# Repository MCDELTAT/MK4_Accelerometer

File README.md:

## Prusa MK4 Accelerometer

If you're reading this it's likely because you've [noticed][3] that your MK4 xBuddy Controller has a port reserved for an accelerometer and wondered "Hmmm. I wonder if that works."

I'm happy to report that the answer is "Yes." I found it to be reliable and working just fine, but in response to my demo, Josef Prusa himself responded "Hi! Please note the code is not tested on MK4 so you shouldn't count on it's results. There will be an official implementation but not ETA yet." Source [here][4].

This repository contains information, designs, and tools for using an accelerometer with the Prusa MK4 3D Printer.

This primary document is focused on being a quick start guide, while other documents in the repository contain more in-depth technical information about other aspects of the project.

## Future Work
Here's a roadmap of a few simple tasks that I'd like to accomplish with this project.

- [x] Design mounts for the Toolhead and Bed that work with both custom and off the shelf boards.
- [x] Test other chips like the LIS3DH for compatibility.
- [ ] Run print tests and document outcomes (IN PROGRESS)
- [ ] Design our own custom PCB with a compatible Molex Clik-MATE connector (IN PROGRESS-Design Complete, Validation Underway)
    * This will allow users to install an accelerometer quickly and without all the tools needed to solder.

## Compatability
* At the moment, only MCDELTAT has confirmed the accelerometer as working on firmware versions 5.2.1 and 6.0.0. Their printer uses the 2021 0.2.7 xBuddy board. Two other community members have tried on printers that use the 0.3.7 board and are not seeing similar signals on their ports. I'm working with them and hoping Prusa will release the older schematics so I can compare.

## ⚠️ HALT - Warranty Check
Q: Does this void my warranty?

A: Probably.

You can read the official Prusa Warranty on their website [here][1]. Quote "This warranty is **voided by:** ... Upgrades or add-ons that are not officially supported."

This modification does not require you to compile or upload any custom firmware to work. The release firmware directly from Prusa supports these boards, so this is purely a hardware addition. That said, I will include thorough warnings where appropriate to ensure that nothing goes wrong, should you follow the instructions correctly.

## Tools and Part Requirements
Here is a list of tools that will be needed to add an accelerometer board at the moment.
1. Clik-MATE 6 Pin Cable Assembly (MPN: 0151350606 for 600mm). Digikey [source][2]
2. LIS2DH Accelerometer board ready for SPI communication.
    * See the table below for a table of boards that have been tested and verified as working.
3. Soldering Iron and related tools.
4. (Optional) A multimeter will be helpful.
5. Mounts for the board. 3D Printable mounts for the X and Y-Axis can be found [here][9]. The mounts are designed for MK4 printers, but the mounting tray is designed to be modular. At the moment the only tray is for the generic accelerometer boards. I will provide another tray for my custom board later.
6. Some kind of computer capable of controlling your MK4 Printer and a USB-C Cable. I tested everything with a Raspberry Pi running Octoprint, but any compatible software should be functional. For example, Mainsail or Pronterface should be more than capable.

## Soldering Your Accelerometer Board
For this section, I will document the soldering procedure for the generic purple Chinese LIS2DH boards, as that is the first board I confirmed to be working.

1. Power off your printer. Unplug it from it's power source. 
2. (Optional but recommended). Insert one end of your cable assembly into the Accelerometer port of the board. The connector is keyed and will only fit one direction, with the release arm facing towards the center of the board (back of the printer). Pull it back out and use a marker to color the top side of the connector. This will help you to keep track of which pin belongs to each cable.
3. Cut the cable assembly with a wire stripper or other tool. Goodbye beautiful connector.
4. Strip off approximately 5mm of the outer wire insulator for each cable.
5. (Optional tinning technique). Heat up your soldering iron, twist the stranded wires of a single cable together tightly, and apply solder to the wires. This makes it into one solid connector and makes it easier to solder to the accelerometer board later.
6. Identify the first wire to solder. If you did step two, the top side that you marked is pin 6 on the Prusa Schematics and Connector documentation. (See the Diagram below). On the Digikey cable assembly, they use tape in the middle of the cables to group them to together. We have two options:

    a) Cut the tape and visually trace the cables.

    b) Leave the tape intact and use a multimeter to buzz out which cable is connected to each connector pin. This can be done by switching to continuity mode, touching one lead to a cable of your choice, and the other to small pad on the back of the connector.
7. Solder the wire to the correct position. Repeat steps 5 and 6, finding the correct wires and soldering them to the board. A table is provided below for reference.
8. Snip the extra wire that wasn't covered by the solder joint.

## Pinout
Here is a reference table for the Prusa Connector Pins and the breakout board. Prusa's documentation supporting this is found [here][5].

| Connector           | Pin (Prusa) | Pin (Accel Board) | Type              | Function | GPIO | Limitations  |
|---------------------|-------------|-------------------|-------------------|----------|------|--------------|
| J29 (ACCELEROMETER) | 1           | CS                | open drain output | SPI2 CS  | PA10 | Max 3.3V/5mA |
| J29 (ACCELEROMETER) | 2           | SCL               | input/output      | SPI2 SCL | PB10 | Max 5V/5mA   |
| J29 (ACCELEROMETER) | 3           | SDA               | input/output      | SPI2 SDI | PC3  | Max 5V/5mA   |
| J29 (ACCELEROMETER) | 4           | SDO               | input/output      | SPI2 SDO | PC2  | Max 5V/5mA   |
| J29 (ACCELEROMETER) | 5           | VCC               | 3V3               | Power    | x    | Max 50mA     |
| J29 (ACCELEROMETER) | 6           | GND               | GND               | Power    | x    | x            |

## Pinout Images
### Connector Side:

### Adafruit Board:

### Generic LIS2DH Board:

## Compatible Boards:

| Board Name                                | Testing Status | Source                                          | Notes                                                                                                                                                                                                                                                                                                       |
|-------------------------------------------|----------------|-------------------------------------------------|-------------------------------------------------------------------------------------------------------------------------------------------------------------------------------------------------------------------------------------------------------------------------------------------------------------|
| NOYITO LIS2DH12TR Development Board       | WORKING        | https://a.co/d/4UiPgB6                          | This board is very generic and can be found many places ranging from $4 to $13. They likely all come from the same place.                                                                                                                                                                                   |
| Sparkfun SPX-15760 LIS2DH12 (Qwiic)       | FAIL           | https://www.sparkfun.com/products/retired/15760 | This board is hard wired for I2C, while the Prusa MK4 expects an SPI compatible device, so this will not work.                                                                                                                                                                                              |
| Adafruit LIS3DH Triple-Axis Accelerometer (Recommended) | WORKING   | https://www.adafruit.com/product/2809           | The LIS3DH has a few more features we won't be using, however I confirmed it to work similarly. Since Adafruit has a solid supply chain, this is likely the best all around choice. Minor Con: The breakout board has pins on both sides, requiring cables to be on both sides, so it is a little messier.

## Using the Accelerometer
If you are hoping to get useful values out of the accelerometer, emphasize doing any pending maintenance first. Lube the smooth rods/bearings. Check for scratches. Check belt tension, etc. Each of these factors will change these results if you fix them later, so just do them now to avoid retesting. See Prusa's official docs for recommended regular maintenance [here][8].

1. Once you are confident your connections are going to the correct pins, plug the accelerometer into the MK4 Buddy board and the mounts.
2. Connect to the printer over USB-C to issue GCODE.
3. ⚠️ **IMPORTANT STEP** Before setting any parameters, gather the values that Prusa originally set on the printer. This will allow you to roll back to those values later if you want. In a GCODE control window, issue the `M593` command with no arguments. This will return the existing Input Shaping (IS) parameters. An example of my output can be found below. If you want to see all my Input Shaping testing results, see [Testing][6].
```
Send: M593
Recv: echo:axis X type=MZV freq=50.700001 damp=0.100000 vr=20.000000
Recv: echo:axis Y type=MZV freq=40.599998 damp=0.100000 vr=20.000000
Recv: echo:axis Z disabled
Recv: echo:weight_adjust y freq_delta=-20.000000 mass_limit=800.000000
Recv: ok
```
4. Issue the following command `M959 X F40.0 G60.0 N10`. This tests the X-Axis starting at 40Hz and ending at 60Hz, with a very quick sample size. The results this produces should not be used. It is provided here purely as a way to quickly test that you wired up the sensor correctly.
5. Now to test the X-Axis, you likely want to run the default workflow, which is over a large frequency range and sample size.
6. The command above gave us a general range, but now we can confirm a second time by running it over a smaller range with more samples. For example, if step 5 returned a frequency of 79.0Hz, then I can test from 65 to 85Hz, at steps of 0.5Hz, with 100 Samples. This can be done with the command `M959 X F65.0 G85.0 H0.5`. See below for a list of parameters to the M959 command.
7. Once you are satisfied with the results and think you have a consistent number, we will save the values. See the official documentation for the `M593` command [here][7]. Assuming I got the following results `Recv: ZV shaper selected Recv: Frequency: 79.00 damping ratio: 0.17444`

    a) To do this temporarily (until you shut off the printer), run the following command `M593 X D0.17444 F79.00 T0`. Note the lack of the `W` parameter, the parameter to save it to the EEPROM.

    b) To save it permanently, run the following command `M593 X D0.17444 F79.00 T0 W`.

## M959 Command
The `M959` command does all the heavy lifting in our testing. It's parameters are only listed in the source code, so I've copied them here for convenience.
```
/\*\*  
 \* u/brief Tune input shaper  
 \*  
 \* - X<direction> Vibrate with X motor, start in direction 1 or -1  
 \* - Y<direction> Vibrate with Y motor, start in direction 1 or -1  
 \* - Z<direction> Vibrate with Z motor, start in direction 1 or -1  
 \* - K           select Klipper tune algorithm  
 \* - KM          select Klipper Marek modified tune algorithm  
 \* - F<Hz>       Start frequency  
 \* - G<Hz>       End frequency  
 \* - H<Hz>       Frequency step  
 \* - A<mm/s-2>   Acceleration  
 \* - N<cycles>   Number of excitation signal periods  
 \*               of active measurement.  
 \*/  
```

[1]: https://help.prusa3d.com/article/warranty_2288
[2]: https://www.digikey.com/en/products/detail/molex/0151350606/6830172
[3]: https://help.prusa3d.com/article/accessory-connectors-mk4_622345
[4]: https://www.reddit.com/r/prusa3d/comments/1b5wych/comment/ktben9d/?utm_source=share&utm_medium=web2x&context=3
[5]: https://help.prusa3d.com/article/accessory-connectors-mk4_622345
[6]: ./Testing.md
[7]: https://help.prusa3d.com/article/buddy-firmware-specific-g-code-commands_633112#m-codes
[8]: https://help.prusa3d.com/article/regular-printer-maintenance-mk4_419000
[9]: https://www.printables.com/model/839201-mk4-accelerometer-mounts-for-x-and-y-axis-input-sh

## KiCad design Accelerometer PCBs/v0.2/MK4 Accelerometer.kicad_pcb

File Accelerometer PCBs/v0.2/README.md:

## Prusa MK4 Accelerometer v0.2

🛑 Status: Design complete, have ordered PCBs, have not tried on a real printer.

This board design fixes a large error made in the last revision, namely, the pinout is correct for a stock cable purchased from Digikey. Thus you should be able to buy cables from them, and immediately plug it into your printer. I also moved a silkscreen around the LIS2DH chip for hopefully better visual alignment. Finally, as reported in issue #1 of the repo, a 2.2K may be added to make this circuit compatible with 0.3.7 and 0.4.4 boards.

This is the bare minimum reference circuit as provided by STMicroelectronics, with an LED for reference.

BOM:
| Label | Digikey Part Num       | Quantity | Description                        |
| ----- | ---------------------- | -------- | ---------------------------------- |
| C1    | 1292-0201X104K250CT-ND | 1        | 0603 100nF Ceramic Capacitor       |
| C2    | CL10A106MQ8NNNC        | 1        | 0603 10uF Ceramic Capacitor        |
| D1    | IN-S63AT5G             | 1        | 0603 Green LED 525nm               |
| R1    | RC0603FR-07120RL       | 1        | 0603 120Ohm Resistor 1/10W         |
| R2    | ERJ-H3GJ222V           | 1        | 0603 2.2K Resistor Panasonic 1/8W  |
| J1    | 5025840670             | 1        | Molex Clickmate 6Pin SMT Connector |
| U1    | LIS2DHTR               | 1        | LIS2DHTR MEMS Accelerometer        |

When aligning the LIS2DHTR by hand, make sure the circle is in the top right corner, matching the stars near the LGA-12 pads.

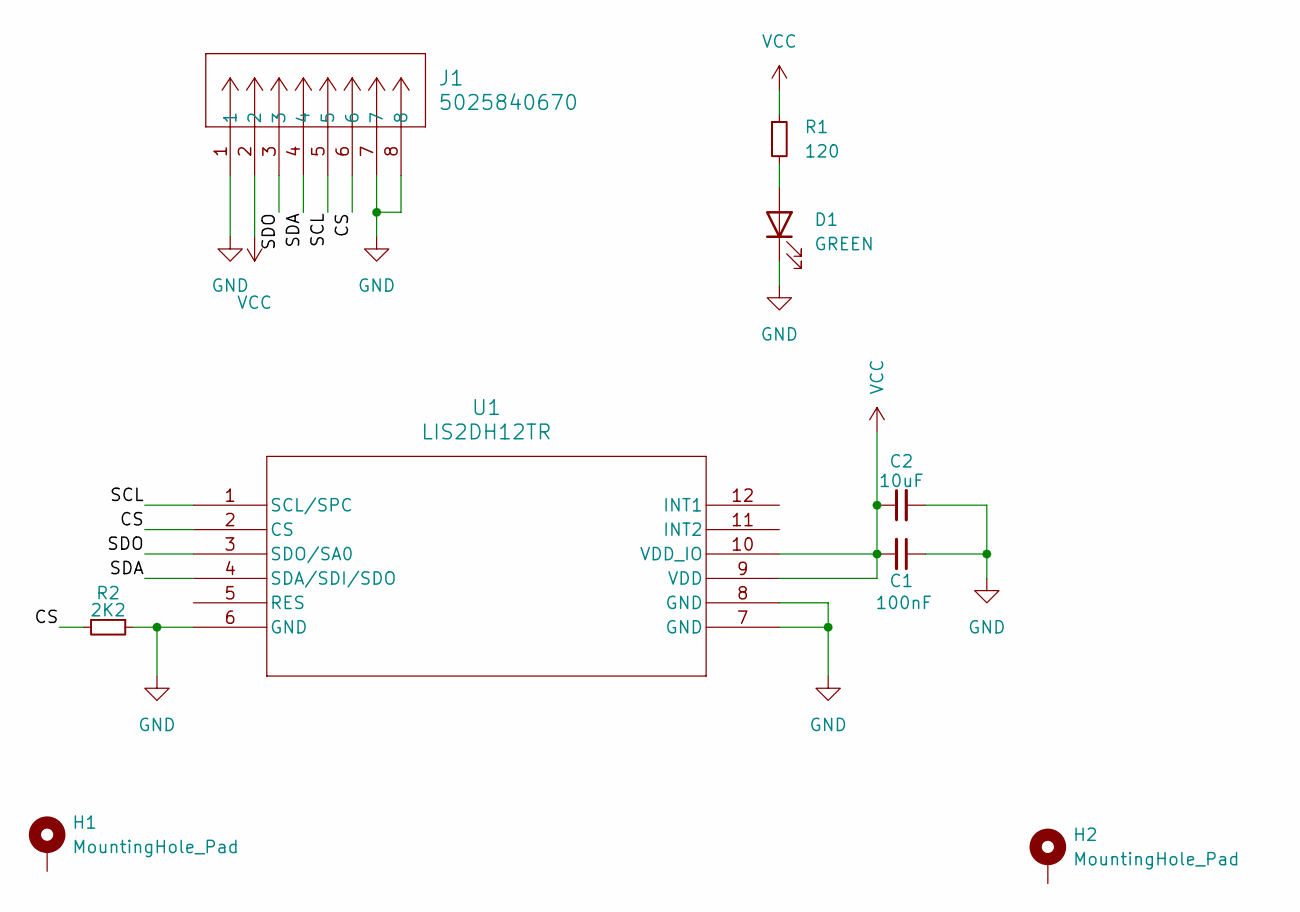
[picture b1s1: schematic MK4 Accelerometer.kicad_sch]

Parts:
C1: 100nF; C_0603_1608Metric
C2: 10uF; C_0603_1608Metric
D1: GREEN; LED_0603_1608Metric
H1, H2: MountingHole_Pad; MountingHole_2.2mm_M2_Pad
J1: 5025840670; CON_5025840670_MOL
R1: 120; R_0603_1608Metric
R2: 2K2; R_0603_1608Metric
U1: LIS2DH12TR; LGA-12_STM

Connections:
/CS: J1.6, R2.2, U1.2 (CS)
/SCL: J1.5, U1.1 (SCL/SPC)
/SDA: J1.4, U1.4 (SDA/SDI/SDO)
/SDO: J1.3, U1.3 (SDO/SA0)
GND: C1.1, C2.2, D1.1 (K), J1.1, J1.7, J1.8, R2.1, U1.6 (GND), U1.7 (GND), U1.8 (GND)
unnamed: D1.2 (A), R1.2
VCC: C1.2, C2.1, J1.2, R1.1, U1.9 (VDD), U1.10 (VDD_IO)

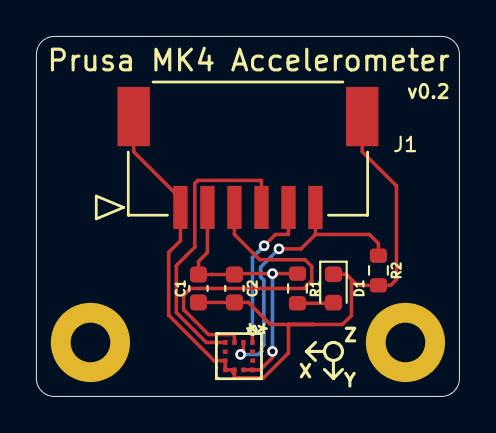
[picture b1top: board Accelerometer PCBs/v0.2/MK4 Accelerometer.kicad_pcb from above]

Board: 2 copper layers, 23.5 x 20.0 mm, 9 parts (0 on the bottom side), 7 nets.

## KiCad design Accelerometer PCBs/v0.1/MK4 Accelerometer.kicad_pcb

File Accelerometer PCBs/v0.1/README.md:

## Prusa MK4 Accelerometer v0.1

🛑 This board was submitted for reference, but it won't work without a custom cable. This is because I got the pins backwards on the Click-mate connector because I had crimped my own. When trying with a stock cable from Digikey, I noticed the error. This will be fixed in the next revision. In other words: don't try to make this one.

This is the bare minimum reference circuit as provided by STMicroelectronics, with an LED for reference.

BOM:
| Digikey Part Num       | Quantity | Description                        |
| ---------------------- | -------- | ---------------------------------- |
| 1292-0201X104K250CT-ND | 1        | 0603 100nF Ceramic Capacitor       |
| CL10A106MQ8NNNC        | 1        | 0603 10uF Ceramic Capacitor        |
| IN-S63AT5G             | 1        | 0603 Green LED 525nm               |
| RC0603FR-07120RL       | 1        | 0603 120Ohm Resistor 1/10W         |
| 5025840670             | 1        | Molex Clickmate 6Pin SMT Connector |
| LIS2DHTR               | 1        | LIS2DHTR MEMS Accelerometer        |

When aligning the LIS2DHTR by hand, make sure the circle is in the top right corner, matching the stars near the LGA-12 pads.

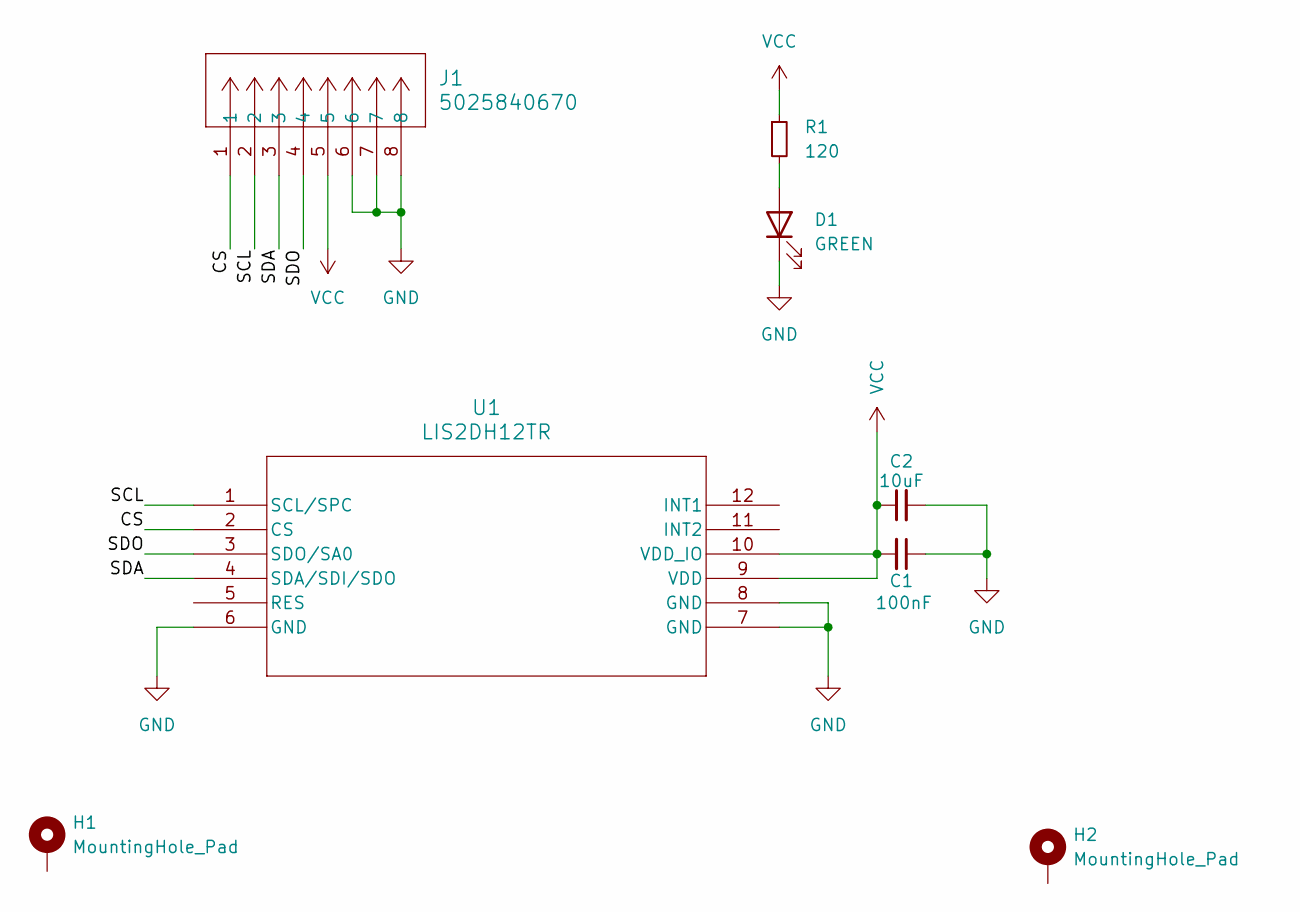
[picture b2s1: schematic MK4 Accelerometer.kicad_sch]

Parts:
C1: 100nF; C_0603_1608Metric
C2: 10uF; C_0603_1608Metric
D1: GREEN; LED_0603_1608Metric
H1, H2: MountingHole_Pad; MountingHole_2.2mm_M2_Pad
J1: 5025840670; CON_5025840670_MOL
R1: 120; R_0603_1608Metric
U1: LIS2DH12TR; LGA-12_STM

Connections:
/CS: J1.1, U1.2 (CS)
/SCL: J1.2, U1.1 (SCL/SPC)
/SDA: J1.3, U1.4 (SDA/SDI/SDO)
/SDO: J1.4, U1.3 (SDO/SA0)
GND: C1.1, C2.2, D1.1 (K), J1.6, J1.7, J1.8, U1.6 (GND), U1.7 (GND), U1.8 (GND)
unnamed: D1.2 (A), R1.2
VCC: C1.2, C2.1, J1.5, R1.1, U1.9 (VDD), U1.10 (VDD_IO)

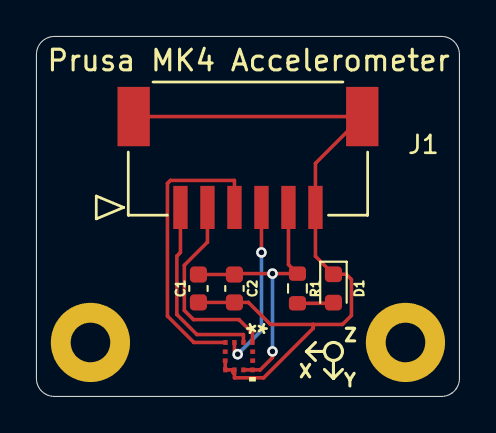
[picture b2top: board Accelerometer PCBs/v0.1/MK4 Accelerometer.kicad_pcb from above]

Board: 2 copper layers, 23.5 x 20.0 mm, 8 parts (0 on the bottom side), 7 nets.

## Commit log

2024-03-10 Initial Document Draft
2024-03-17 Update test results, fix some styling typos.
2024-04-15 Update cable link, add tests in Klipper mode
2024-04-15 Link to the 3D printed mounts
2024-04-17 Add Signal Capture information
2024-04-17 Spelling, clarification and fix link
2024-04-18 Document Adafruit LIS3DH board as working
2024-05-03 Images + compatability + clarifications
2024-05-17 Added v0.1 of PCB
2024-05-25 0.2 PCB
